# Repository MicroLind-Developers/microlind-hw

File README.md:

# microlind-hw
Hardware repository for the microlind project

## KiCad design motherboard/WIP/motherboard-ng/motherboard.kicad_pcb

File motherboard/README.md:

This i the location for the final µLind 6x09 motherboard hw files

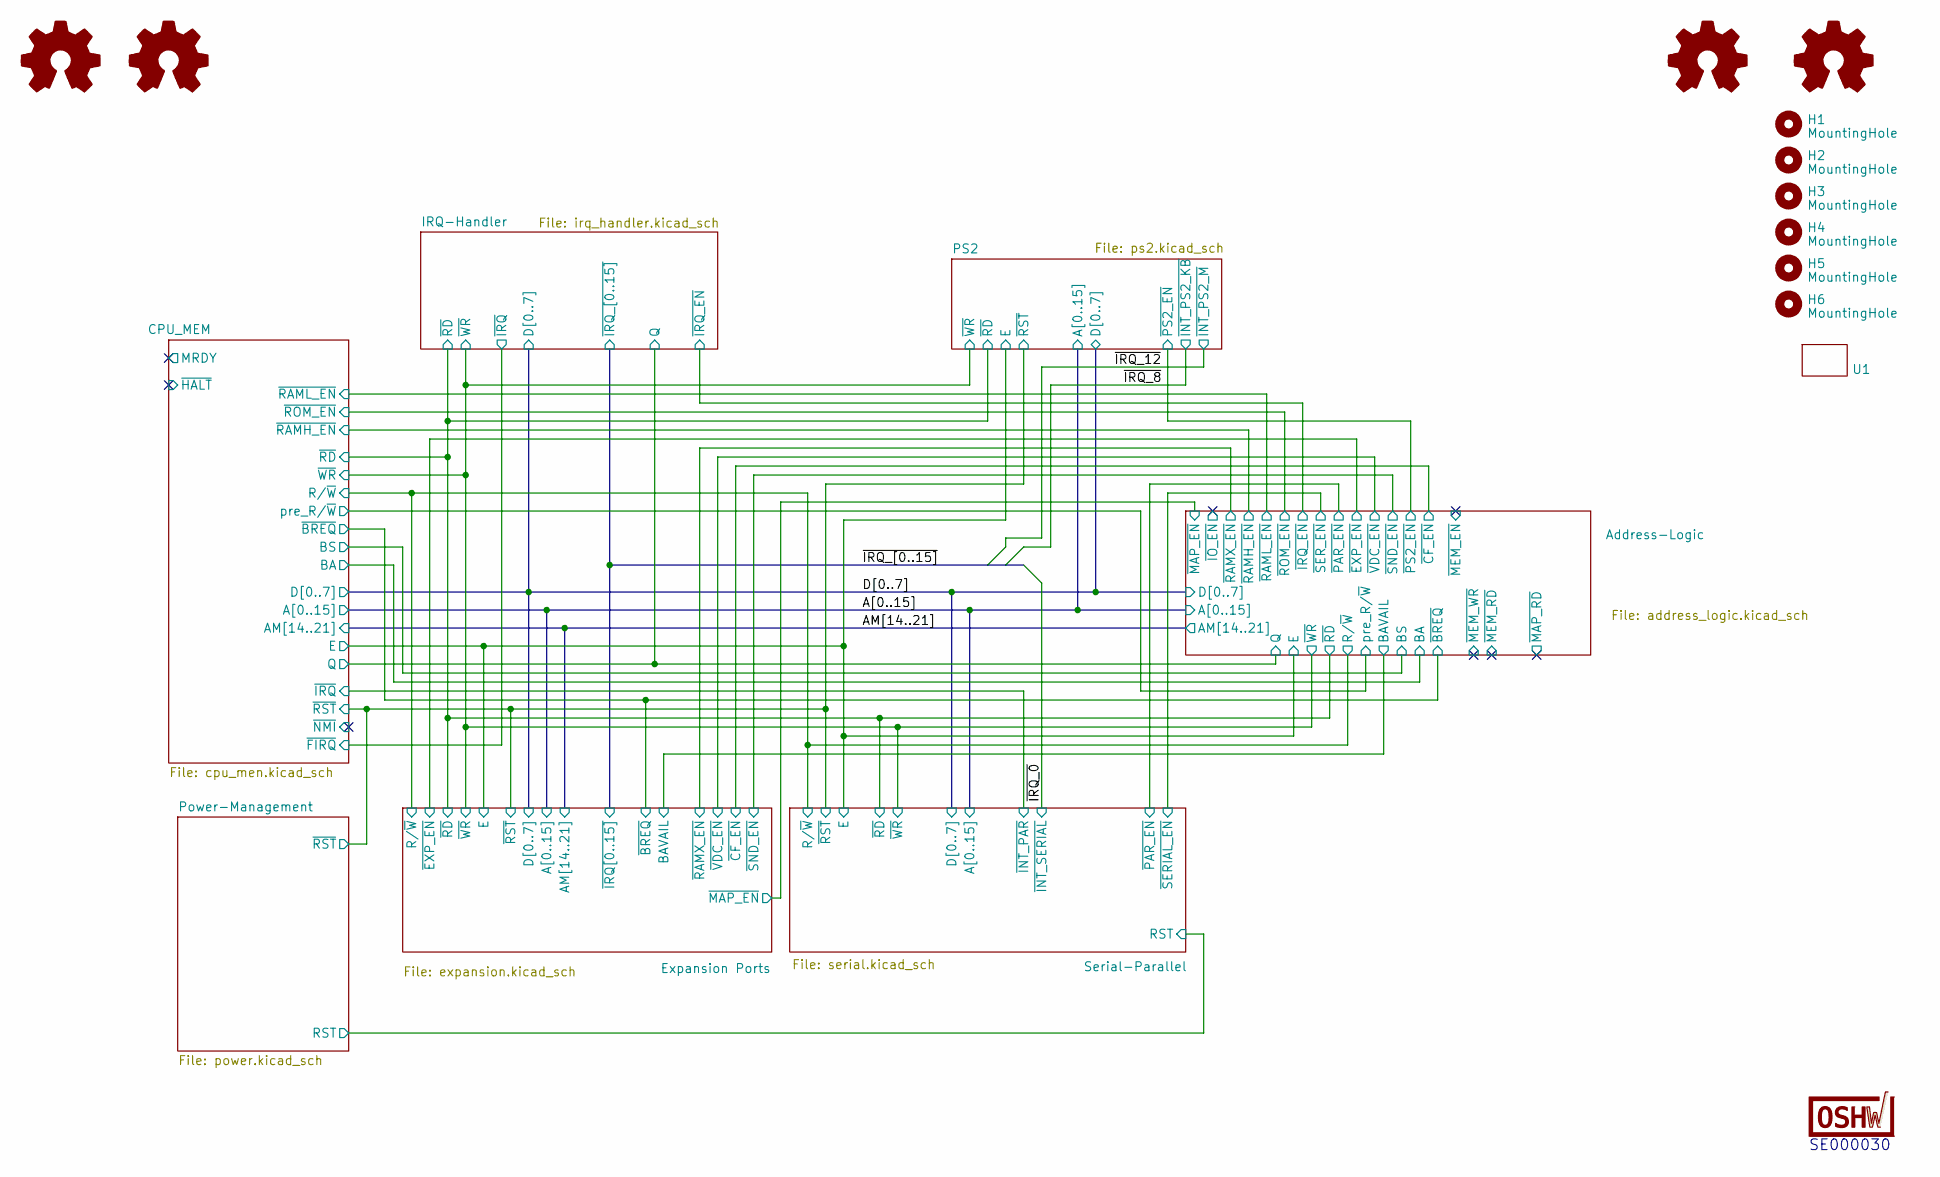
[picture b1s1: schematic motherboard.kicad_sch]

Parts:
H1, H2, H3, H4, H5, H6: MountingHole; MountingHole_3.2mm_M3_ISO7380
LOGO1: (no value)
U1: mITX

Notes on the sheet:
SE000030

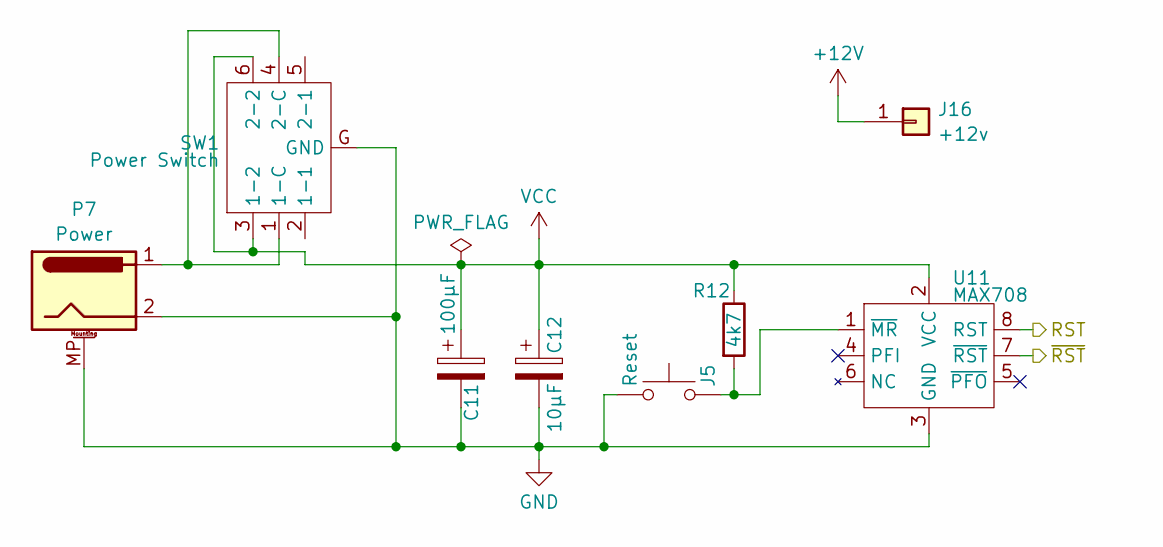
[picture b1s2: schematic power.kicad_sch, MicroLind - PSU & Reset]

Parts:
C11: 100µF; CP_Radial_D6.3mm_P2.50mm
C12: 10µF; CP_Radial_D4.0mm_P2.00mm
J5: Reset; PinHeader_1x02_P2.54mm_Vertical
J16: +12v; PinHeader_1x01_P2.54mm_Vertical
P7: Power; BarrelJack_CUI_PJ-063AH_Horizontal
R12: 4k7; R_Axial_DIN0204_L3.6mm_D1.6mm_P7.62mm_Horizontal
SW1: Power Switch; CMD-Switch
U11: MAX708; DIP-8_W7.62mm_Socket

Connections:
+12V: J16.1; also elsewhere on the board
/Expansion Ports/~RST: U11.7 (~RST); also elsewhere on the board
/Power-Management/RST: U11.8 (RST); also elsewhere on the board
unnamed: P7.1, SW1.1 (1-C), SW1.4 (2-C)
unnamed: J5.2, R12.2, U11.1 (~MR)

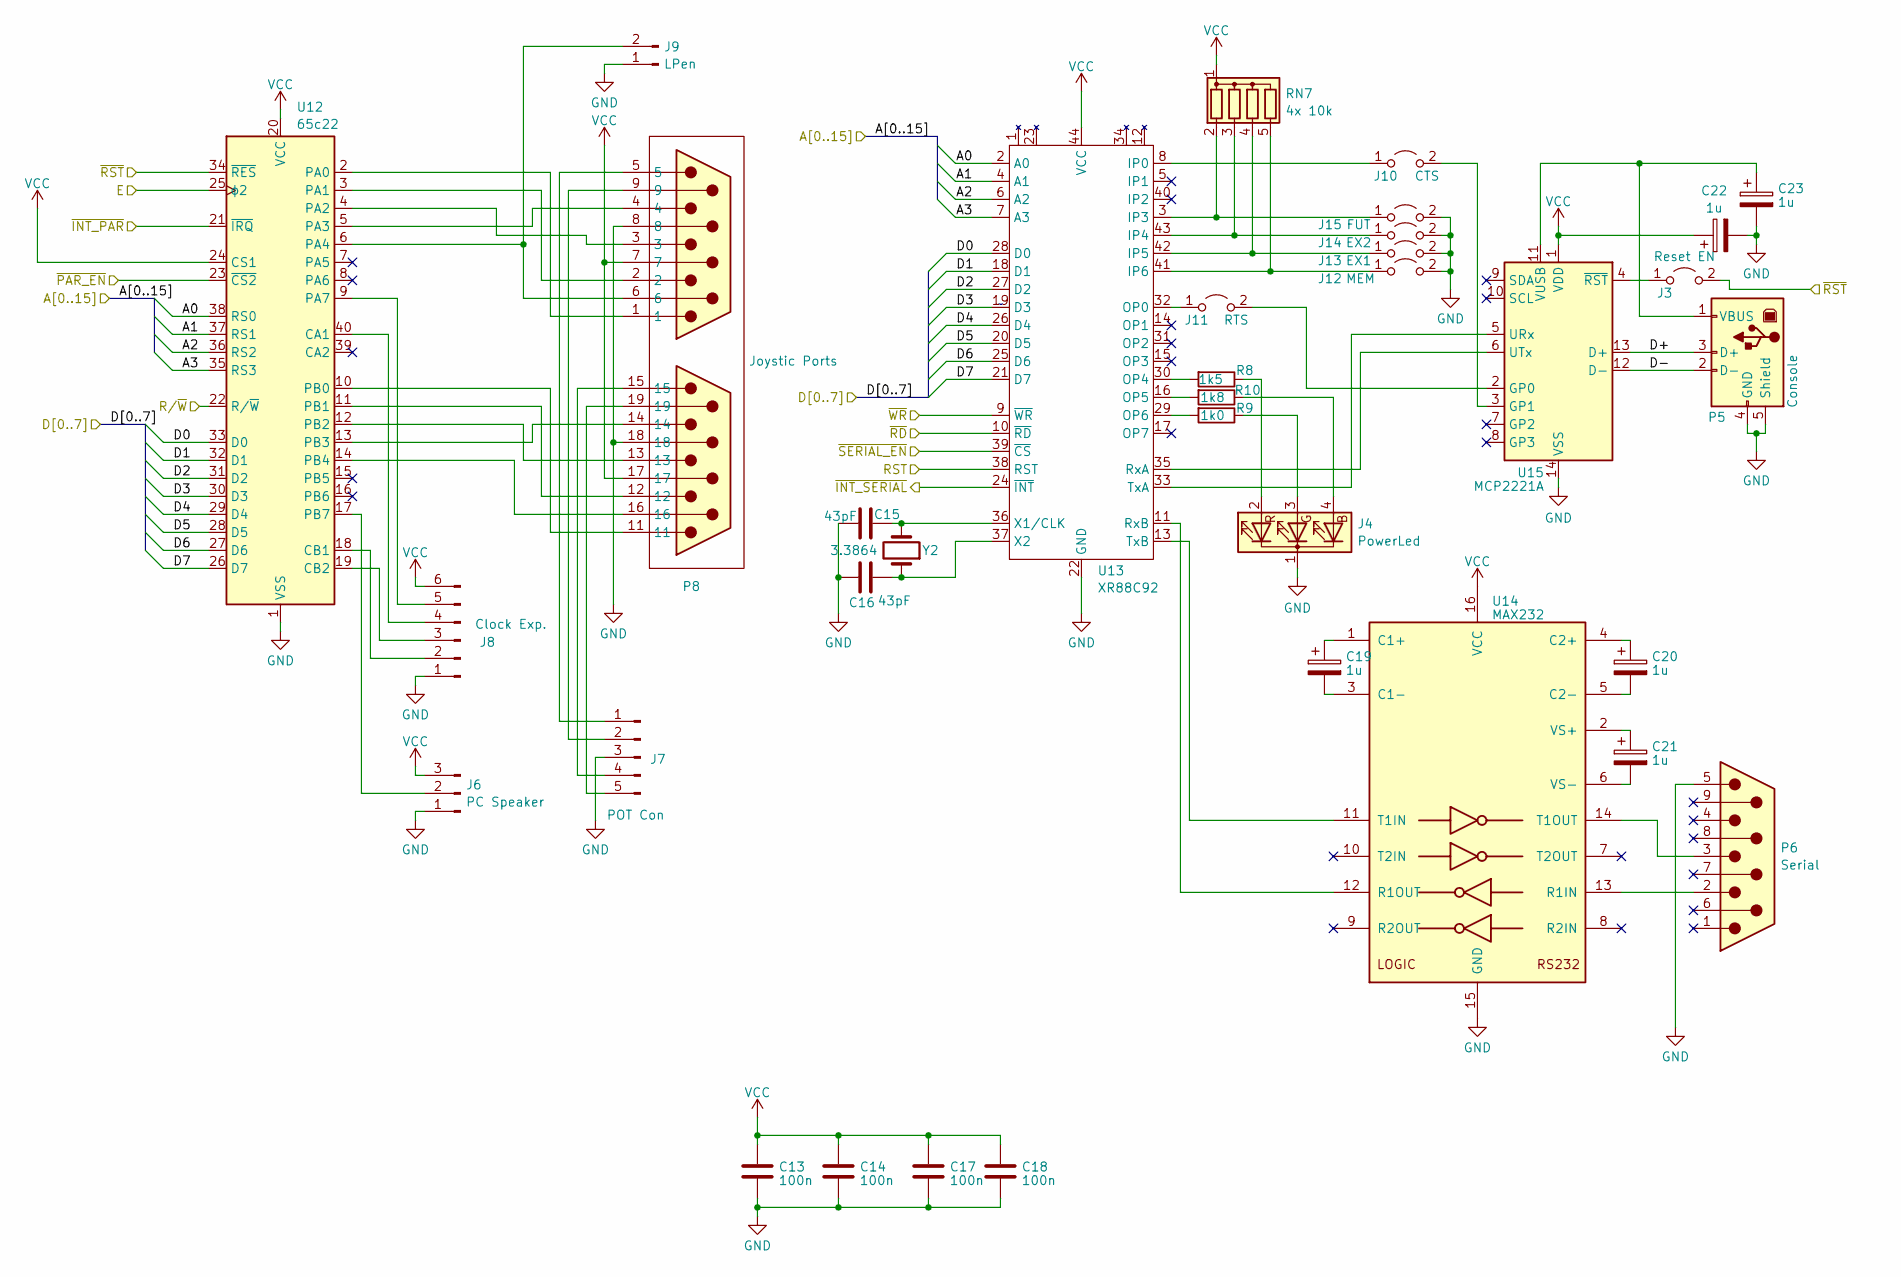
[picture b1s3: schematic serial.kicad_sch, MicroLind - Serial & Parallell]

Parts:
C13, C14, C17, C18: 100n; C_Disc_D5.0mm_W2.5mm_P2.50mm
C15, C16: 43pF; C_Disc_D5.0mm_W2.5mm_P2.50mm
C19, C20, C21, C22, C23: 1u; CP_Radial_D4.0mm_P2.00mm
J3: Reset EN; PinHeader_1x02_P2.54mm_Vertical
J4: PowerLed; PinHeader_1x04_P2.54mm_Vertical
J6: PC Speaker; PinHeader_1x03_P2.54mm_Vertical
J7: POT Con; PinHeader_1x05_P2.54mm_Vertical
J8: Clock Exp.; PinHeader_1x06_P2.54mm_Vertical
J9: LPen; PinHeader_1x02_P2.54mm_Vertical
J10: CTS; PinHeader_1x02_P2.54mm_Vertical
J11: RTS; PinHeader_1x02_P2.54mm_Vertical
J12: MEM; PinHeader_1x02_P2.54mm_Vertical
J13: EX1; PinHeader_1x02_P2.54mm_Vertical
J14: EX2; PinHeader_1x02_P2.54mm_Vertical
J15: FUT; PinHeader_1x02_P2.54mm_Vertical
P5: Console; USB_B_Lumberg_2411_02_Horizontal
P6: Serial; 23018431
P8: Joystic Ports; DSUB-9-Double_NorComp
R8: 1k5; R_Axial_DIN0204_L3.6mm_D1.6mm_P7.62mm_Horizontal
R9: 1k0; R_Axial_DIN0204_L3.6mm_D1.6mm_P7.62mm_Horizontal
R10: 1k8; R_Axial_DIN0204_L3.6mm_D1.6mm_P7.62mm_Horizontal
RN7: 4x 10k; R_Array_SIP5
U12: 65c22; DIP-40_W15.24mm_Socket
U13: XR88C92; PLCC-44_THT-Socket
U14: MAX232; DIP-16_W7.62mm_Socket
U15: MCP2221A; DIP-14_W7.62mm_Socket
Y2: 3.3864; Crystal_HC49-U_Vertical

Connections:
/A0: U12.38 (RS0), U13.2 (A0); also elsewhere on the board
/A1: U12.37 (RS1), U13.4 (A1); also elsewhere on the board
/A2: U12.36 (RS2), U13.6 (A2); also elsewhere on the board
/A3: U12.35 (RS3), U13.7 (A3); also elsewhere on the board
/Address-Logic/~PAR_EN: U12.23 (~CS2); also elsewhere on the board
/Address-Logic/~SER_EN: U13.39 (~CS); also elsewhere on the board
/CPU_MEM/~IRQ: U12.21 (~IRQ); also elsewhere on the board
/D0: U12.33 (D0), U13.28 (D0); also elsewhere on the board
/D1: U12.32 (D1), U13.18 (D1); also elsewhere on the board
/D2: U12.31 (D2), U13.27 (D2); also elsewhere on the board
/D3: U12.30 (D3), U13.19 (D3); also elsewhere on the board
/D4: U12.29 (D4), U13.26 (D4); also elsewhere on the board
/D5: U12.28 (D5), U13.20 (D5); also elsewhere on the board
/D6: U12.27 (D6), U13.25 (D6); also elsewhere on the board
/D7: U12.26 (D7), U13.21 (D7); also elsewhere on the board
/Expansion Ports/E: U12.25 (ϕ2); also elsewhere on the board
/Expansion Ports/R/~W: U12.22 (R/~W); also elsewhere on the board
/Expansion Ports/~RD: U13.10 (~RD); also elsewhere on the board
/Expansion Ports/~RST: J3.2 (B), U12.34 (~RES); also elsewhere on the board
/Expansion Ports/~WR: U13.9 (~WR); also elsewhere on the board
/Power-Management/RST: U13.38 (RST); also elsewhere on the board
/Serial-Parallel/D+: P5.3 (D+), U15.13 (D+)
/Serial-Parallel/D-: P5.2 (D-), U15.12 (D-)
/~IRQ_0: U13.24 (~INT); also elsewhere on the board
unnamed: J3.1 (A), U15.4 (~RST)
unnamed: J4.4 (BA), R10.1
unnamed: J4.3 (GA), R9.1
unnamed: J4.2 (RA), R8.1
unnamed: J6.2, U12.17 (PB7)
unnamed: J7.1, P8.5
unnamed: J7.2, P8.9
unnamed: J7.4, P8.15
unnamed: J7.5, P8.19
unnamed: J8.2, U12.18 (CB1)
unnamed: J8.3, U12.19 (CB2)
unnamed: J8.4, U12.40 (CA1)
unnamed: J8.5, U12.9 (PA7)
unnamed: J9.2, P8.6, U12.6 (PA4)
unnamed: J10.1 (A), U13.8 (IP0)
unnamed: J10.2 (B), U15.3 (GP1)
unnamed: J11.1 (A), U13.32 (OP0)
unnamed: J11.2 (B), U15.2 (GP0)
unnamed: J12.1 (A), RN7.5 (R4), U13.41 (IP6)
unnamed: J13.1 (A), RN7.4 (R3), U13.42 (IP5)
unnamed: J14.1 (A), RN7.3 (R2), U13.43 (IP4)
unnamed: J15.1 (A), RN7.2 (R1), U13.3 (IP3)
unnamed: C23.1, P5.1 (VBUS), U15.11 (VUSB)
unnamed: P8.1, U12.2 (PA0)
unnamed: P8.2, U12.3 (PA1)
unnamed: P8.3, U12.4 (PA2)
unnamed: P8.4, U12.5 (PA3)
unnamed: P8.11, U12.10 (PB0)
unnamed: P8.12, U12.11 (PB1)
unnamed: P8.13, U12.12 (PB2)
unnamed: P8.14, U12.13 (PB3)
unnamed: P8.16, U12.14 (PB4)
unnamed: R8.2, U13.30 (OP4)
unnamed: R10.2, U13.16 (OP5)
unnamed: R9.2, U13.29 (OP6)
unnamed: U13.35 (RxA), U15.6 (UTx)
unnamed: U13.11 (RxB), U14.12 (R1OUT)
unnamed: U13.33 (TxA), U15.5 (URx)
unnamed: U13.13 (TxB), U14.11 (T1IN)
unnamed: C15.1, U13.36 (X1/CLK), Y2.2
unnamed: C16.1, U13.37 (X2), Y2.1
unnamed: C19.1, U14.1 (C1+)
unnamed: C19.2, U14.3 (C1-)
unnamed: C20.1, U14.4 (C2+)
unnamed: C20.2, U14.5 (C2-)
unnamed: P6.2, U14.13 (R1IN)
unnamed: P6.3, U14.14 (T1OUT)
unnamed: C21.1, U14.2 (VS+)
unnamed: C21.2, U14.6 (VS-)

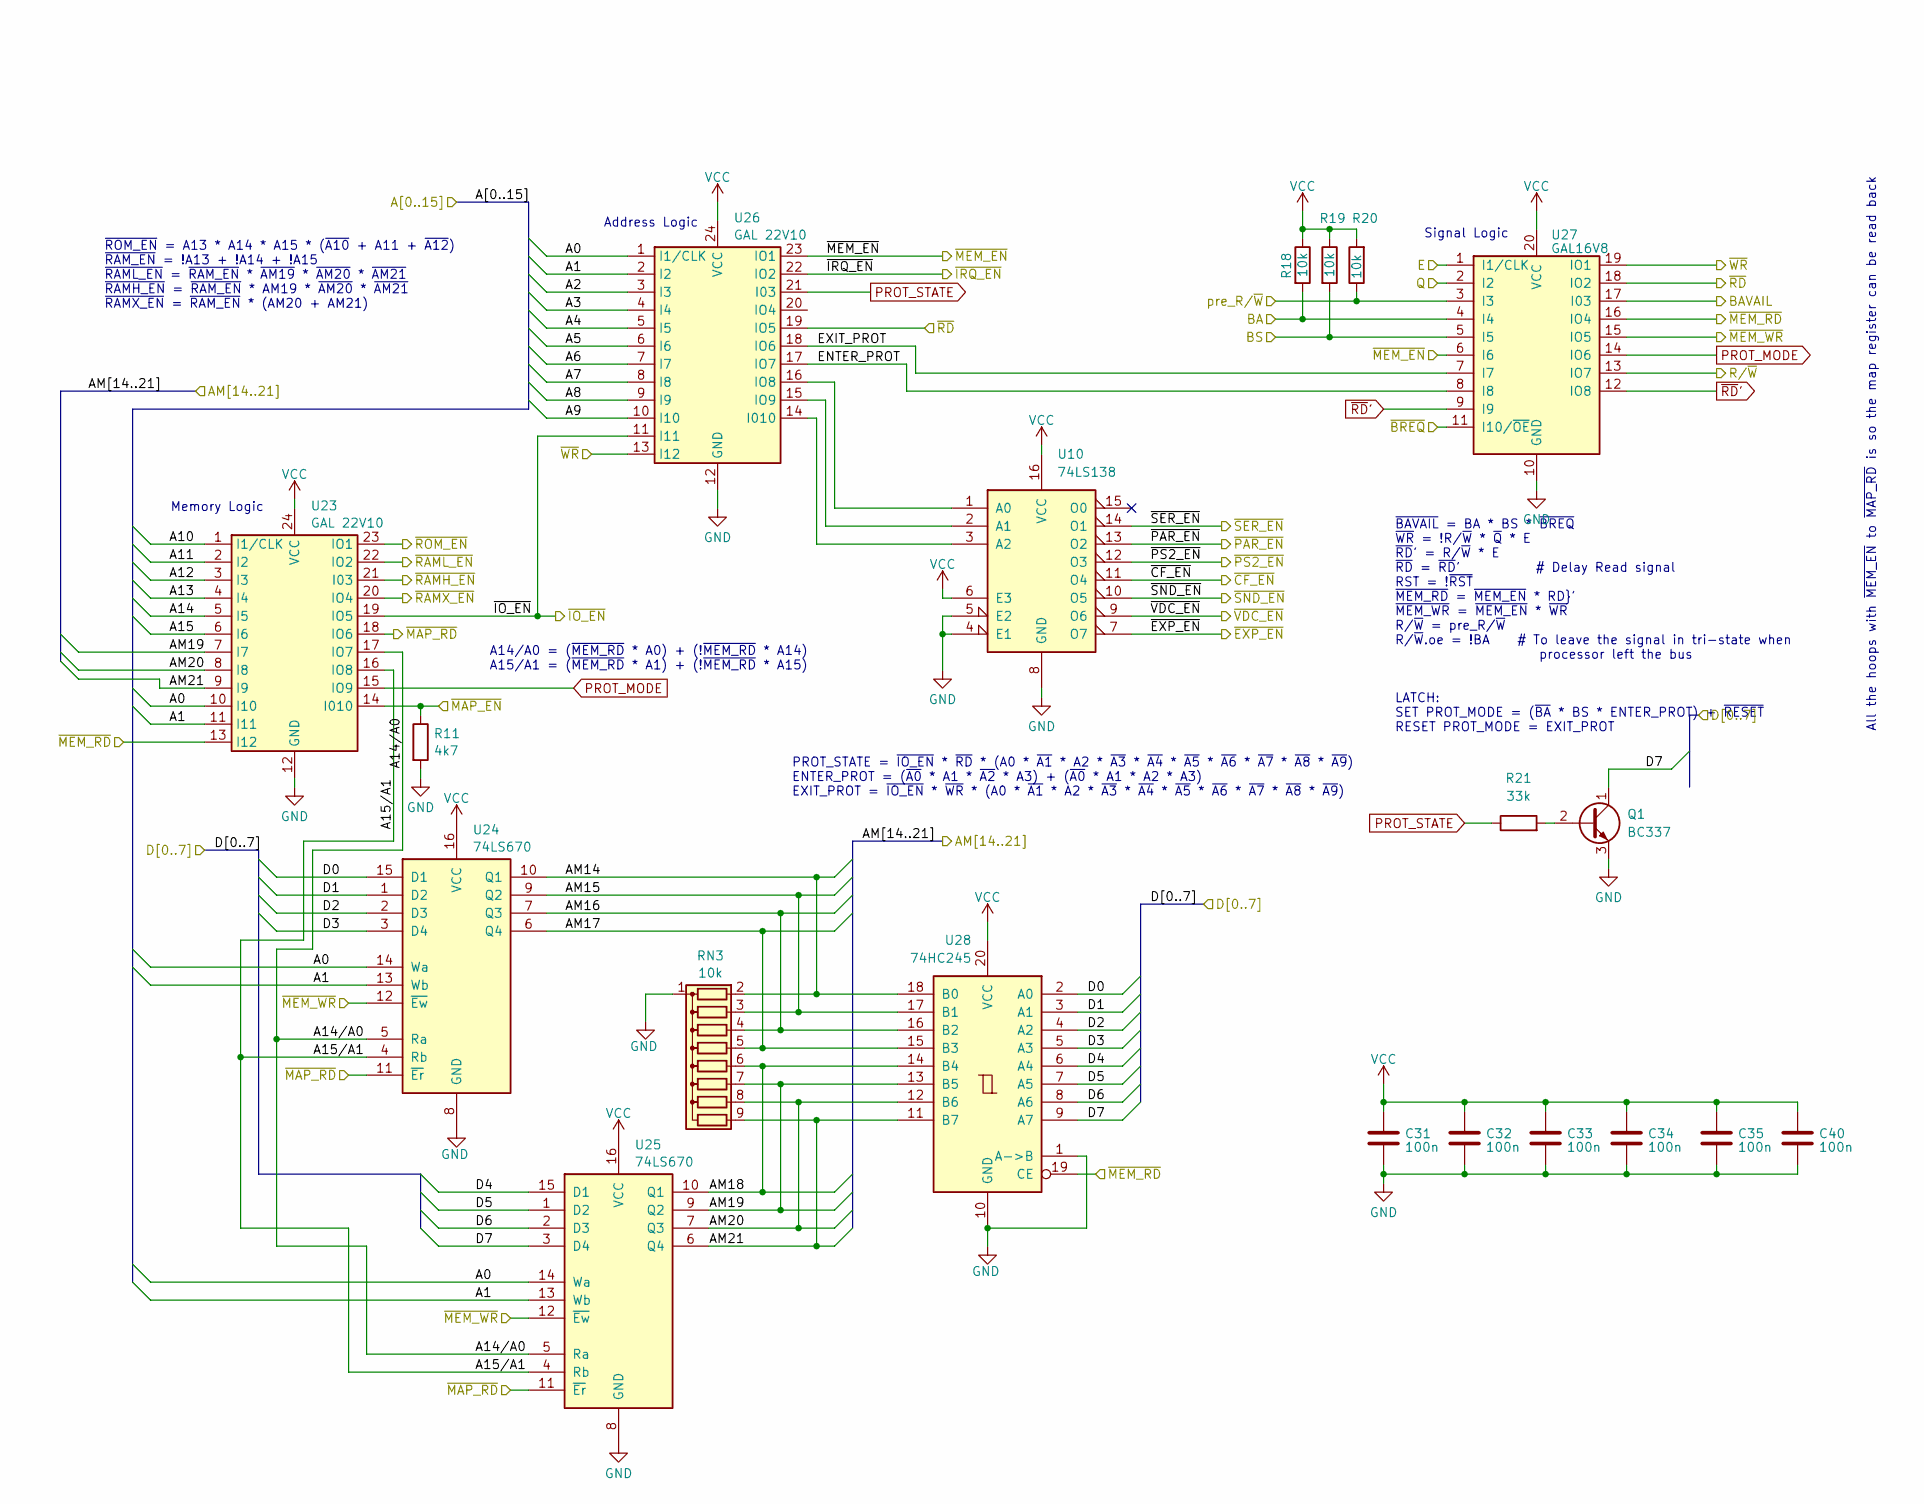
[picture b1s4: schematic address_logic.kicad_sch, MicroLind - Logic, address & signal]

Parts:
C31, C32, C33, C34, C35, C40: 100n; C_Disc_D5.0mm_W2.5mm_P2.50mm
Q1: BC337; TO-92_Inline
R11: 4k7; R_Axial_DIN0204_L3.6mm_D1.6mm_P7.62mm_Horizontal
R18, R19, R20: 10k; R_Axial_DIN0204_L3.6mm_D1.6mm_P7.62mm_Horizontal
R21: 33k; R_Axial_DIN0204_L3.6mm_D1.6mm_P7.62mm_Horizontal
RN3: 10k; R_Array_SIP9
U10: 74LS138; DIP-16_W7.62mm_Socket
U23, U26: GAL 22V10; DIP-24_W7.62mm_Socket
U24, U25: 74LS670; DIP-16_W7.62mm_Socket
U27: GAL16V8; DIP-20_W7.62mm_Socket
U28: 74HC245; DIP-20_W7.62mm_Socket

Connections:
/A0: U23.10 (I10), U24.14 (Wa), U25.14 (Wa), U26.1 (I1/CLK); also elsewhere on the board
/A1: U23.11 (I11), U24.13 (Wb), U25.13 (Wb), U26.2 (I2); also elsewhere on the board
/A2: U26.3 (I3); also elsewhere on the board
/A3: U26.4 (I4); also elsewhere on the board
/A4: U26.5 (I5); also elsewhere on the board
/A5: U26.6 (I6); also elsewhere on the board
/A6: U26.7 (I7); also elsewhere on the board
/A7: U26.8 (I8); also elsewhere on the board
/A8: U26.9 (I9); also elsewhere on the board
/A9: U26.10 (I10); also elsewhere on the board
/A10: U23.1 (I1/CLK); also elsewhere on the board
/A11: U23.2 (I2); also elsewhere on the board
/A12: U23.3 (I3); also elsewhere on the board
/A13: U23.4 (I4); also elsewhere on the board
/A14: U23.5 (I5); also elsewhere on the board
/A15: U23.6 (I6); also elsewhere on the board
/AM14: RN3.2 (R1), U24.10 (Q1), U28.18 (B0); also elsewhere on the board
/AM15: RN3.3 (R2), U24.9 (Q2), U28.17 (B1); also elsewhere on the board
/AM16: RN3.4 (R3), U24.7 (Q3), U28.16 (B2); also elsewhere on the board
/AM17: RN3.5 (R4), U24.6 (Q4), U28.15 (B3); also elsewhere on the board
/AM18: RN3.6 (R5), U25.10 (Q1), U28.14 (B4); also elsewhere on the board
/AM19: RN3.7 (R6), U23.7 (I7), U25.9 (Q2), U28.13 (B5); also elsewhere on the board
/AM20: RN3.8 (R7), U23.8 (I8), U25.7 (Q3), U28.12 (B6); also elsewhere on the board
/AM21: RN3.9 (R8), U23.9 (I9), U25.6 (Q4), U28.11 (B7); also elsewhere on the board
/Address-Logic/A14/A0: U23.17 (IO7), U24.5 (Ra), U25.5 (Ra)
/Address-Logic/A15/A1: U23.16 (IO8), U24.4 (Rb), U25.4 (Rb)
/Address-Logic/BA: R18.2, U27.4 (I4); also elsewhere on the board
/Address-Logic/BS: R19.2, U27.5 (I5); also elsewhere on the board
/Address-Logic/ENTER_PROT: U26.17 (IO7), U27.8 (I8)
/Address-Logic/EXIT_PROT: U26.18 (IO6), U27.7 (I7)
/Address-Logic/Q: U27.2 (I2); also elsewhere on the board
/Address-Logic/pre_R/~W: R20.1, U27.3 (I3); also elsewhere on the board
/Address-Logic/~CF_EN: U10.11 (O4); also elsewhere on the board
/Address-Logic/~EXP_EN: U10.7 (O7); also elsewhere on the board
/Address-Logic/~IO_EN: U23.19 (IO5), U26.11 (I11)
/Address-Logic/~IRQ_EN: U26.22 (IO2); also elsewhere on the board
/Address-Logic/~MAP_RD: U23.18 (IO6), U24.11 (~Er), U25.11 (~Er)
/Address-Logic/~MEM_EN: U26.23 (IO1), U27.6 (I6)
/Address-Logic/~MEM_RD: U23.13 (I12), U27.16 (IO4), U28.19 (CE)
/Address-Logic/~MEM_WR: U24.12 (~Ew), U25.12 (~Ew), U27.15 (IO5)
/Address-Logic/~PAR_EN: U10.13 (O2); also elsewhere on the board
/Address-Logic/~PS2_EN: U10.12 (O3); also elsewhere on the board
/Address-Logic/~RAMH_EN: U23.21 (I03); also elsewhere on the board
/Address-Logic/~RAML_EN: U23.22 (IO2); also elsewhere on the board
/Address-Logic/~ROM_EN: U23.23 (IO1); also elsewhere on the board
/Address-Logic/~SER_EN: U10.14 (O1); also elsewhere on the board
/Address-Logic/~SND_EN: U10.10 (O5); also elsewhere on the board
/Address-Logic/~VDC_EN: U10.9 (O6); also elsewhere on the board
/D0: U24.15 (D1), U28.2 (A0); also elsewhere on the board
/D1: U24.1 (D2), U28.3 (A1); also elsewhere on the board
/D2: U24.2 (D3), U28.4 (A2); also elsewhere on the board
/D3: U24.3 (D4), U28.5 (A3); also elsewhere on the board
/D4: U25.15 (D1), U28.6 (A4); also elsewhere on the board
/D5: U25.1 (D2), U28.7 (A5); also elsewhere on the board
/D6: U25.2 (D3), U28.8 (A6); also elsewhere on the board
/D7: Q1.1 (C), U25.3 (D4), U28.9 (A7); also elsewhere on the board
/Expansion Ports/BAVAIL: U27.17 (I03); also elsewhere on the board
/Expansion Ports/E: U27.1 (I1/CLK); also elsewhere on the board
/Expansion Ports/R/~W: U27.13 (IO7); also elsewhere on the board
/Expansion Ports/~BREQ: U27.11 (I10/~OE); also elsewhere on the board
/Expansion Ports/~MAP_EN: R11.1, U23.14 (I010); also elsewhere on the board
/Expansion Ports/~RAMX_EN: U23.20 (IO4); also elsewhere on the board
/Expansion Ports/~RD: U26.19 (IO5), U27.18 (IO2); also elsewhere on the board
/Expansion Ports/~WR: U26.13 (I12), U27.19 (IO1); also elsewhere on the board
unnamed: Q1.2 (B), R21.2
unnamed: U10.1 (A0), U26.16 (IO8)
unnamed: U10.2 (A1), U26.15 (IO9)
unnamed: U10.3 (A2), U26.14 (I010)
PROT_MODE: U23.15 (IO9), U27.14 (IO6)
PROT_STATE: R21.1, U26.21 (I03)
~RD': U27.9 (I9), U27.12 (IO8)

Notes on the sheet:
Memory Logic
A14/A0 = (~{MEM_RD} * A0) + (!~{MEM_RD} * A14) A15/A1 = (~{MEM_RD} * A1) + (!~{MEM_RD} * A15)
PROT_STATE = ~{IO_EN} * ~{RD} * (A0 * ~{A1} * A2 * ~{A3} * ~{A4} * ~{A5} * ~{A6} * ~{A7} * ~{A8} * ~{A9}) ENTER_PROT = (~{A0} * A1 * ~{A2} * A3) + (~{A0} * A1 * A2 * A3) EXIT_PROT = ~{IO_EN} * ~{WR} * (A0 * ~{A1} * A2 * ~{A3} * ~{A4} * ~{A5} * ~{A6} * ~{A7} * ~{A8} * ~{A9})
~{BAVAIL} = BA * BS * ~{BREQ} ~{WR} = !R/~{W} * ~{Q} * E ~{RD}' = R/~{W} * E ~{RD} = ~{RD}' # Delay Read signal RST = !~{RST} ~{MEM_RD} = ~{MEM_EN} * RD}' ~{MEM_WR} = ~{MEM_EN} * ~{WR} R/~{W} = pre_R/~{W} R/~{W}.oe = !BA # To leave the signal in tri-state when processor left the bus LATCH: SET PROT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
Signal Logic
All the hoops with ~{MEM_EN} to ~{MAP_RD} is so the map register can be read back
Address Logic
~{ROM_EN} = A13 * A14 * A15 * (~{A10} + A11 + ~{A12}) ~{RAM_EN} = !A13 + !A14 + !A15 ~{RAML_EN} = ~{RAM_EN} * ~{AM19} * ~{AM20} * ~{AM21} ~{RAMH_EN} = ~{RAM_EN} * AM19 * ~{AM20} * ~{AM21} ~{RAMX_EN} = ~{RAM_EN} * (AM20 + AM21)

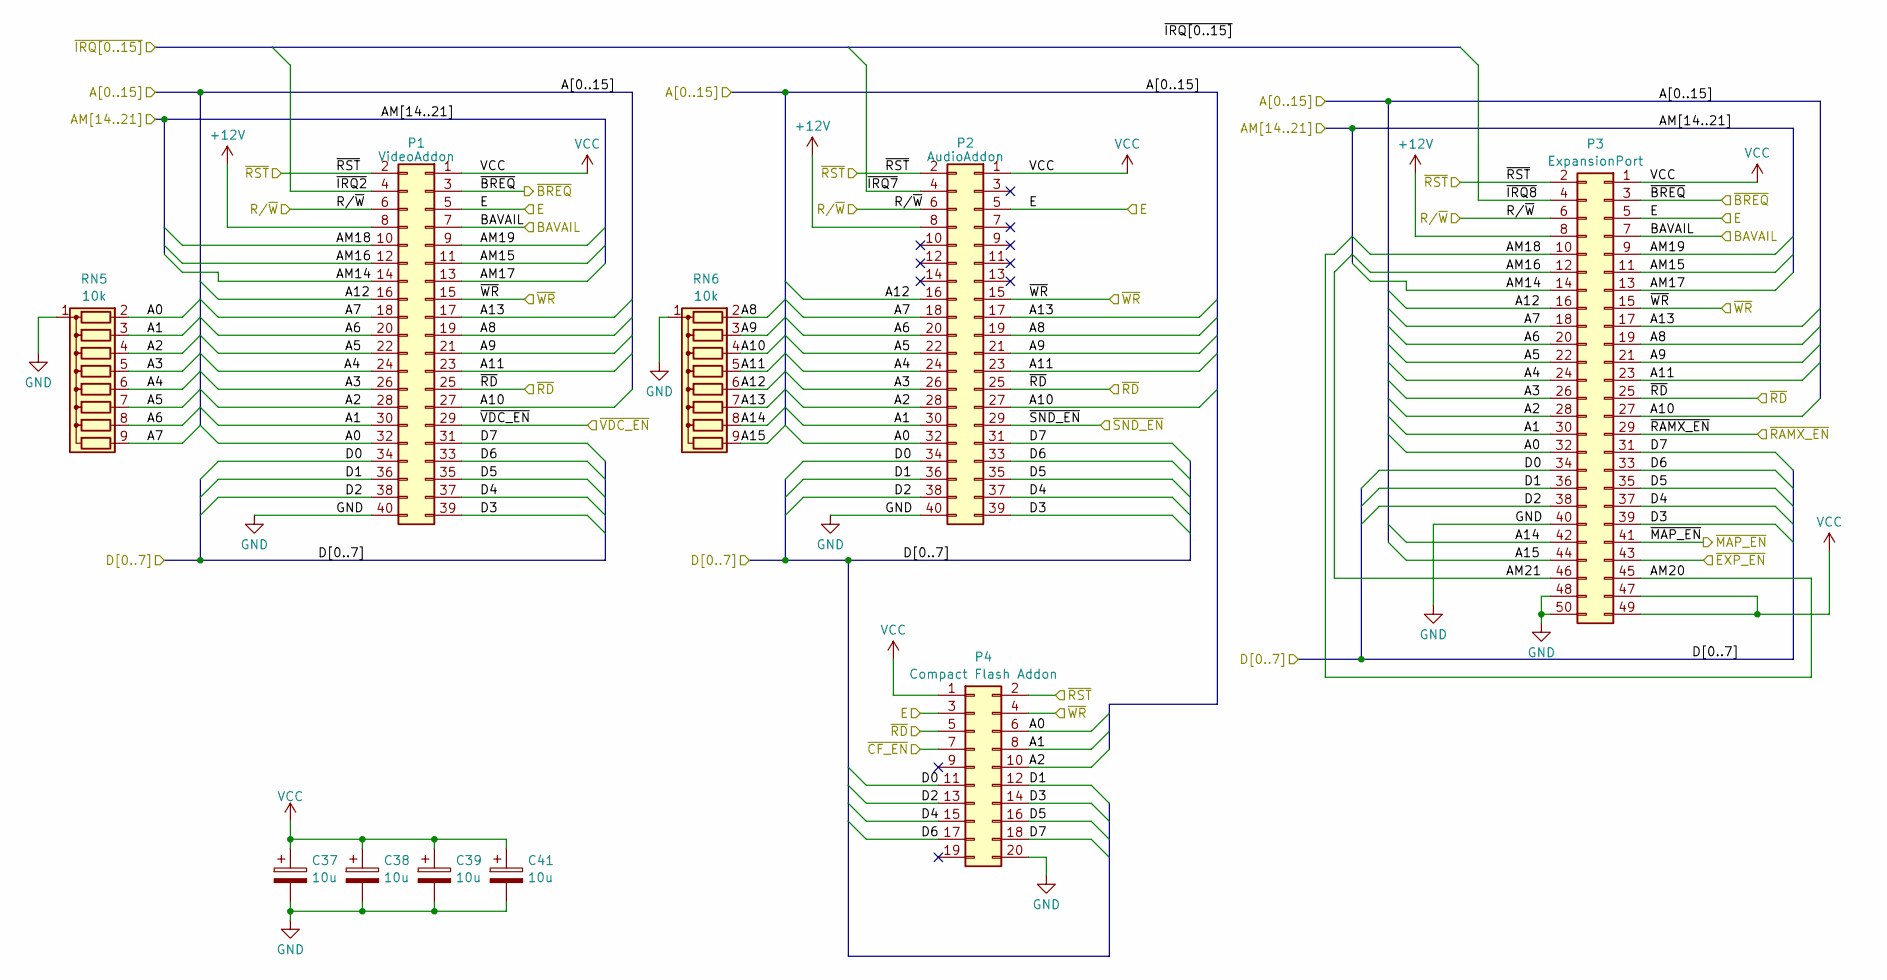
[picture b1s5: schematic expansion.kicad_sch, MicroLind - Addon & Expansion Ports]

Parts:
C37, C38, C39, C41: 10u; CP_Radial_D4.0mm_P2.00mm
P1: VideoAddon; PinSocket_2x20_P2.54mm_Vertical
P2: AudioAddon; PinSocket_2x20_P2.54mm_Vertical
P3: ExpansionPort; PinSocket_2x25_P2.54mm_Vertical
P4: Compact Flash Addon; PinSocket_2x10_P2.54mm_Vertical
RN5, RN6: 10k; R_Array_SIP9

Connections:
+12V: P1.8, P2.8, P3.8; also elsewhere on the board
/A0: P1.32, P2.32, P3.32, P4.6, RN5.2 (R1); also elsewhere on the board
/A1: P1.30, P2.30, P3.30, P4.8, RN5.3 (R2); also elsewhere on the board
/A2: P1.28, P2.28, P3.28, P4.10, RN5.4 (R3); also elsewhere on the board
/A3: P1.26, P2.26, P3.26, RN5.5 (R4); also elsewhere on the board
/A4: P1.24, P2.24, P3.24, RN5.6 (R5); also elsewhere on the board
/A5: P1.22, P2.22, P3.22, RN5.7 (R6); also elsewhere on the board
/A6: P1.20, P2.20, P3.20, RN5.8 (R7); also elsewhere on the board
/A7: P1.18, P2.18, P3.18, RN5.9 (R8); also elsewhere on the board
/A8: P1.19, P2.19, P3.19, RN6.2 (R1); also elsewhere on the board
/A9: P1.21, P2.21, P3.21, RN6.3 (R2); also elsewhere on the board
/A10: P1.27, P2.27, P3.27, RN6.4 (R3); also elsewhere on the board
/A11: P1.23, P2.23, P3.23, RN6.5 (R4); also elsewhere on the board
/A12: P1.16, P2.16, P3.16, RN6.6 (R5); also elsewhere on the board
/A13: P1.17, P2.17, P3.17, RN6.7 (R6); also elsewhere on the board
/A14: P3.42, RN6.8 (R7); also elsewhere on the board
/A15: P3.44, RN6.9 (R8); also elsewhere on the board
/AM14: P1.14, P3.14; also elsewhere on the board
/AM15: P1.11, P3.11; also elsewhere on the board
/AM16: P1.12, P3.12; also elsewhere on the board
/AM17: P1.13, P3.13; also elsewhere on the board
/AM18: P1.10, P3.10; also elsewhere on the board
/AM19: P1.9, P3.9; also elsewhere on the board
/AM20: P3.45; also elsewhere on the board
/AM21: P3.46; also elsewhere on the board
/Address-Logic/~CF_EN: P4.7; also elsewhere on the board
/Address-Logic/~EXP_EN: P3.43; also elsewhere on the board
/Address-Logic/~SND_EN: P2.29; also elsewhere on the board
/Address-Logic/~VDC_EN: P1.29; also elsewhere on the board
/D0: P1.34, P2.34, P3.34, P4.11; also elsewhere on the board
/D1: P1.36, P2.36, P3.36, P4.12; also elsewhere on the board
/D2: P1.38, P2.38, P3.38, P4.13; also elsewhere on the board
/D3: P1.39, P2.39, P3.39, P4.14; also elsewhere on the board
/D4: P1.37, P2.37, P3.37, P4.15; also elsewhere on the board
/D5: P1.35, P2.35, P3.35, P4.16; also elsewhere on the board
/D6: P1.33, P2.33, P3.33, P4.17; also elsewhere on the board
/D7: P1.31, P2.31, P3.31, P4.18; also elsewhere on the board
/Expansion Ports/BAVAIL: P1.7, P3.7; also elsewhere on the board
/Expansion Ports/E: P1.5, P2.5, P3.5, P4.3; also elsewhere on the board
/Expansion Ports/R/~W: P1.6, P2.6, P3.6; also elsewhere on the board
/Expansion Ports/~BREQ: P1.3, P3.3; also elsewhere on the board
/Expansion Ports/~MAP_EN: P3.41; also elsewhere on the board
/Expansion Ports/~RAMX_EN: P3.29; also elsewhere on the board
/Expansion Ports/~RD: P1.25, P2.25, P3.25, P4.5; also elsewhere on the board
/Expansion Ports/~RST: P1.2, P2.2, P3.2, P4.2; also elsewhere on the board
/Expansion Ports/~WR: P1.15, P2.15, P3.15, P4.4; also elsewhere on the board
/~IRQ_2: P1.4; also elsewhere on the board
/~IRQ_7: P2.4; also elsewhere on the board
/~IRQ_8: P3.4; also elsewhere on the board

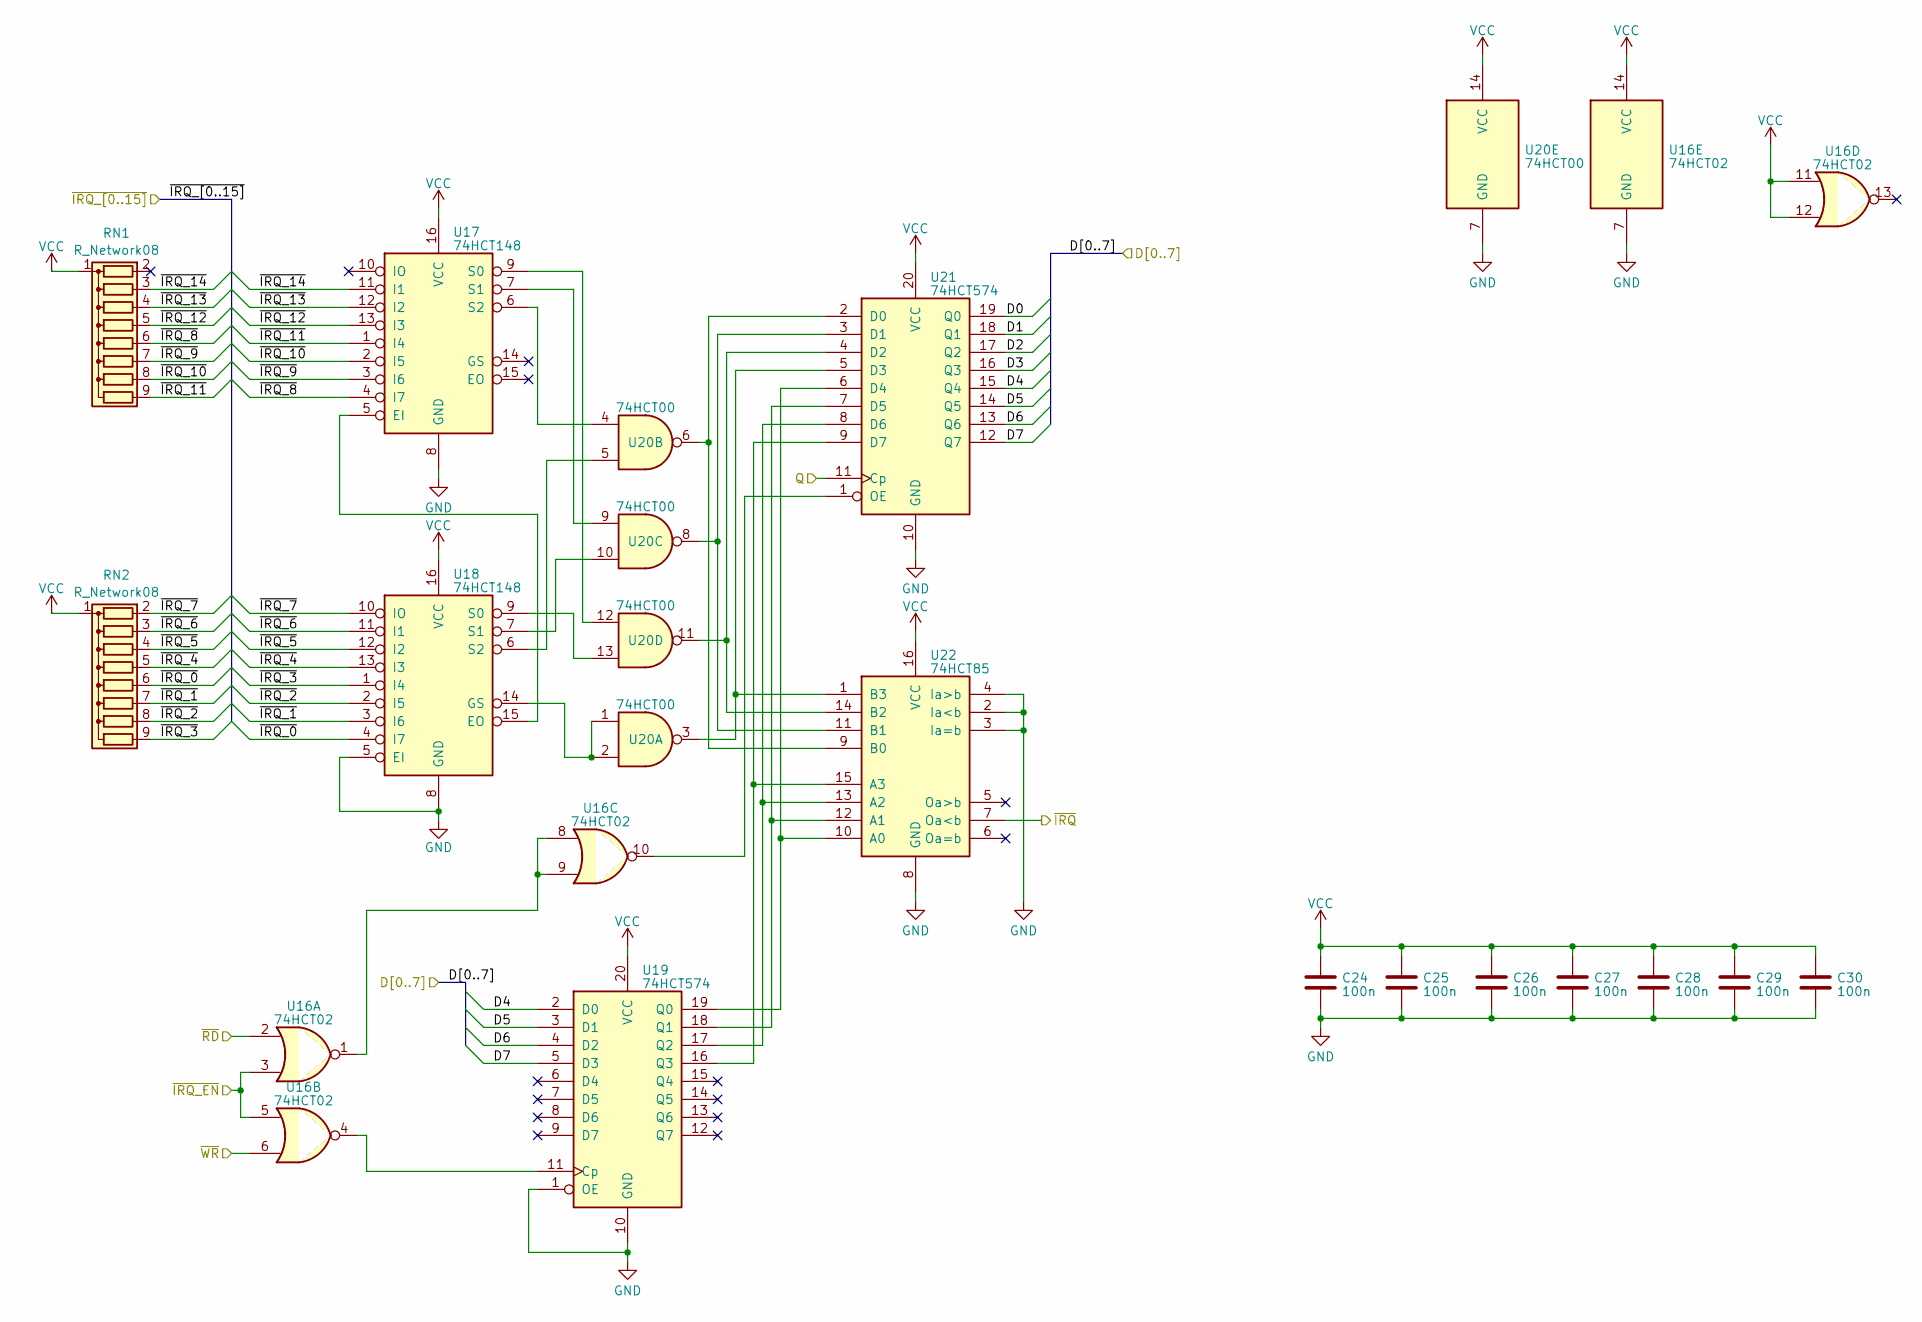
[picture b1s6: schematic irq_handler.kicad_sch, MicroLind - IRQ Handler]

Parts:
C24, C25, C26, C27, C28, C29, C30: 100n; C_Disc_D5.0mm_W2.5mm_P2.50mm
RN1, RN2: R_Network08; R_Array_SIP9
U16: 74HCT02; DIP-14_W7.62mm_Socket
U17, U18: 74HCT148; DIP-16_W7.62mm_Socket
U19, U21: 74HCT574; DIP-20_W7.62mm_Socket
U20: 74HCT00; DIP-14_W7.62mm_Socket
U22: 74HCT85; DIP-16_W7.62mm_Socket

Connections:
/Address-Logic/Q: U21.11 (Cp); also elsewhere on the board
/Address-Logic/~IRQ_EN: U16.3, U16.5; also elsewhere on the board
/CPU_MEM/~FIRQ: U16.13; also elsewhere on the board
/D0: U21.19 (Q0); also elsewhere on the board
/D1: U21.18 (Q1); also elsewhere on the board
/D2: U21.17 (Q2); also elsewhere on the board
/D3: U21.16 (Q3); also elsewhere on the board
/D4: U19.2 (D0), U21.15 (Q4); also elsewhere on the board
/D5: U19.3 (D1), U21.14 (Q5); also elsewhere on the board
/D6: U19.4 (D2), U21.13 (Q6); also elsewhere on the board
/D7: U19.5 (D3), U21.12 (Q7); also elsewhere on the board
/Expansion Ports/~RD: U16.2; also elsewhere on the board
/Expansion Ports/~WR: U16.6; also elsewhere on the board
/~IRQ_0: RN2.6 (R5), U18.4 (I7); also elsewhere on the board
/~IRQ_1: RN2.7 (R6), U18.3 (I6)
/~IRQ_2: RN2.8 (R7), U18.2 (I5); also elsewhere on the board
/~IRQ_3: RN2.9 (R8), U18.1 (I4)
/~IRQ_4: RN2.5 (R4), U18.13 (I3)
/~IRQ_5: RN2.4 (R3), U18.12 (I2)
/~IRQ_6: RN2.3 (R2), U18.11 (I1)
/~IRQ_7: RN2.2 (R1), U18.10 (IO); also elsewhere on the board
/~IRQ_8: RN1.6 (R5), U17.4 (I7); also elsewhere on the board
/~IRQ_9: RN1.7 (R6), U17.3 (I6)
/~IRQ_10: RN1.8 (R7), U17.2 (I5)
/~IRQ_11: RN1.9 (R8), U17.1 (I4)
/~IRQ_12: RN1.5 (R4), U17.13 (I3); also elsewhere on the board
/~IRQ_13: RN1.4 (R3), U17.12 (I2)
/~IRQ_14: RN1.3 (R2), U17.11 (I1)
unnamed: U16.1, U16.8, U16.9
unnamed: U17.5 (EI), U18.15 (EO)
unnamed: U17.9 (S0), U20.12
unnamed: U17.7 (S1), U20.9
unnamed: U17.6 (S2), U20.4
unnamed: U18.14 (GS), U20.1, U20.2
unnamed: U18.9 (S0), U20.13
unnamed: U18.7 (S1), U20.10
unnamed: U18.6 (S2), U20.5
unnamed: U16.4, U19.11 (Cp)
unnamed: U19.19 (Q0), U21.6 (D4), U22.10 (A0)
unnamed: U19.18 (Q1), U21.7 (D5), U22.12 (A1)
unnamed: U19.17 (Q2), U21.8 (D6), U22.13 (A2)
unnamed: U19.16 (Q3), U21.9 (D7), U22.15 (A3)
unnamed: U20.6, U21.2 (D0), U22.9 (B0)
unnamed: U20.8, U21.3 (D1), U22.11 (B1)
unnamed: U20.11, U21.4 (D2), U22.14 (B2)
unnamed: U20.3, U21.5 (D3), U22.1 (B3)
unnamed: U16.10, U21.1 (OE)

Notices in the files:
motherboard/WIP/motherboard-ng/motherboard.kicad_pcb:
Licensed under CERN-OHL-P v2.0
peripherals/WIP/TestCard/TestCard.kicad_sch:
If you chose to manufacture products based on this design, please notify me (see license section 4.2) via info@microlind.io.
